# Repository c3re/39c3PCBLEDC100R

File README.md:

# 39c3PCBLEDC100R

The 39c3PCBLEDC100 is a Coaster for your drinks with option for LED and microcontroller upgrade. By stacking the coasters, you can also build nice blinky towers.

## Rev.0

### Electrical connections

Important: Do not power the board by USB and an external power supply at the same time!
The Din pin of the first LED is connected to pin D4 (GPIO2) of the Wemos D1 mini. ...well, not directly: there is a MOS-FET Transistor in between to shift the signal level from 3.3V to 5V. 
Two of the mounting holes are connected to GND, two of the holes are connected to 5V. You can use this feature to stack multiple 39c3PCBLEDc100R Boards with brass spacers.

The button is connected to D3 (GPIO0) and GND. In WLED (Time & Macros -> Button actions) you can configure actions for short, long and double click.

## License
    
39c3PCBLEDC100R © 2025 by c3RE is licensed under CC BY 4.0. To view a copy of this license,   
visit http://creativecommons.org/licenses/by/4.0/

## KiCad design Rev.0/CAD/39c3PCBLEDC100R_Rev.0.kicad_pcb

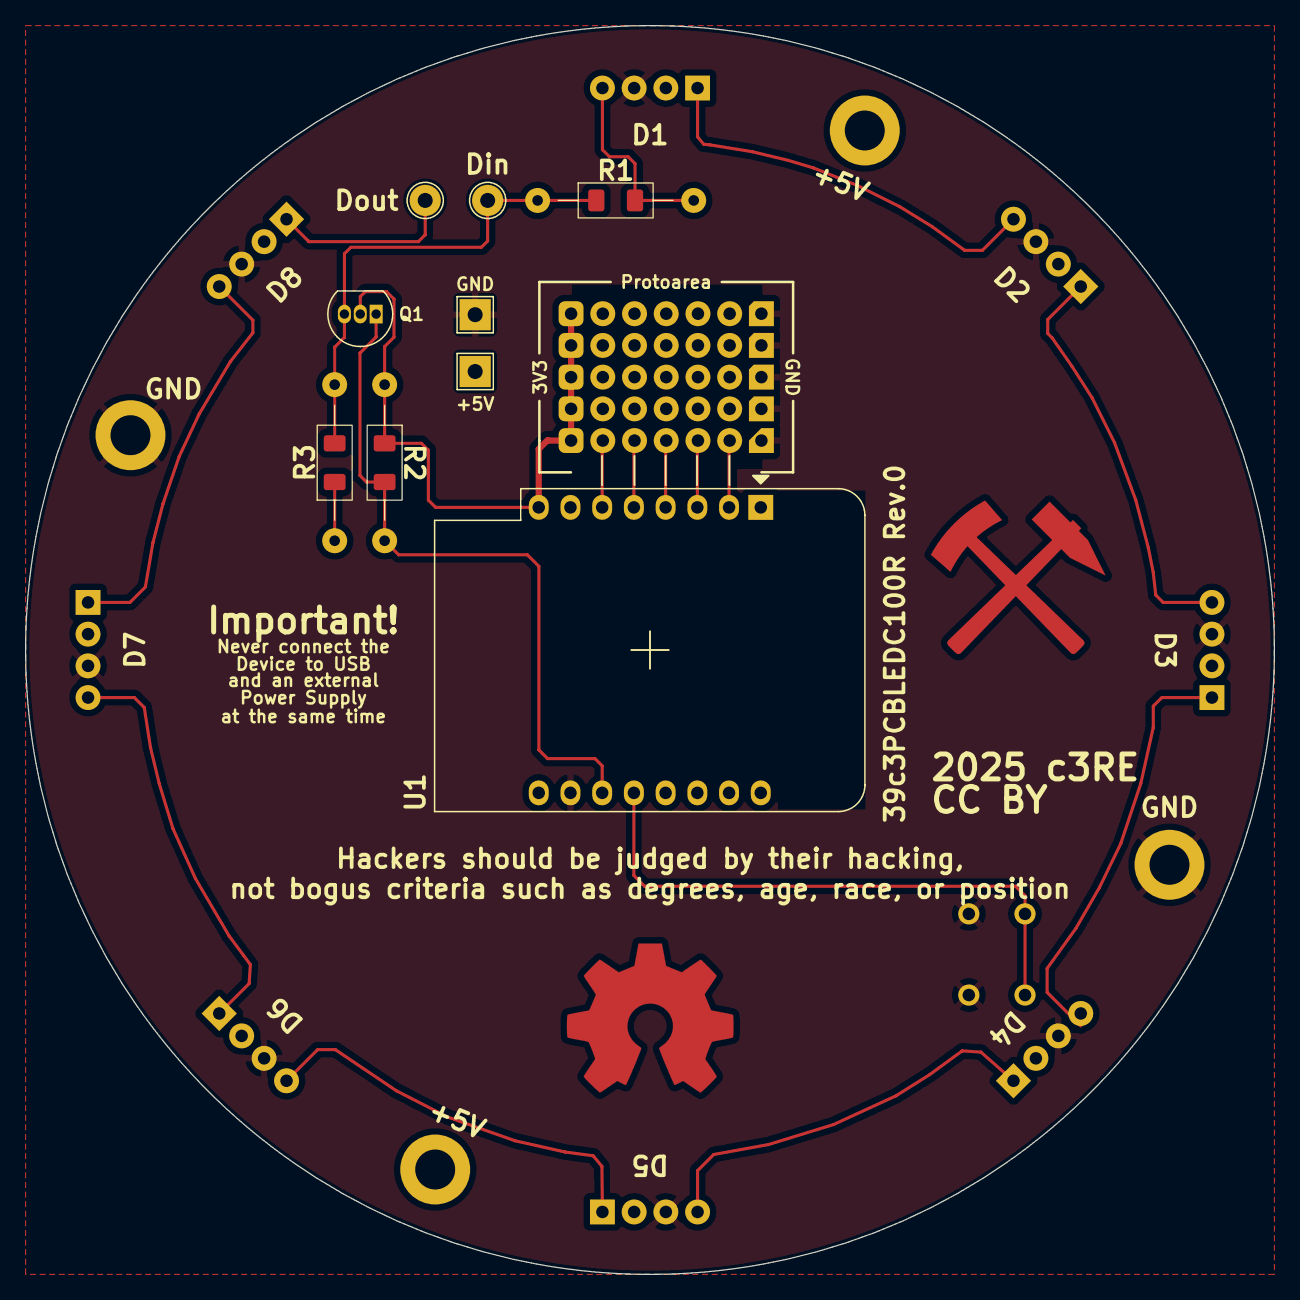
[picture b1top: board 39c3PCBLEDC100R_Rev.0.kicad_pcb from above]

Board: 2 copper layers, 100.0 x 100.0 mm, 23 parts (1 on the bottom side), 20 nets.

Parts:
+5V, +5V#2: +5V; MountingHole_3.2mm_M3_DIN965_Pad
+5V#3: +5V; TestPoint_THTPad_2.5x2.5mm_Drill1.2mm
A1: Protoarea
D1, D2, D3, D4, D5, D6, D7, D8: WS2812D-F5; WS2812_THT
Din: Din; TestPoint_THTPad_D2.5mm_Drill1.2mm
Dout: Dout; TestPoint_THTPad_D2.5mm_Drill1.2mm
GND: GND; MountingHole_3.2mm_M3_DIN965_Pad
GND#2: GND; TestPoint_THTPad_2.5x2.5mm_Drill1.2mm
GND#3: GND; MountingHole_3.2mm_M3_DIN965_Pad
Q1: ZVNL110A; TO-92_Inline
R1: 100; 1206_combi_handsolder
R2, R3: 10k; 1206_combi_handsolder
SW1: SW_SPST; SW_TH_Tactile_Omron_B3F-102x
U1: WeMos_D1_mini; WEMOS_D1_mini_light

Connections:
+5V: +5V.1, +5V#2.1, +5V#3.1, D1.2 (VCC), D2.2 (VCC), D3.2 (VCC), D4.2 (VCC), D5.2 (VCC), D6.2 (VCC), D7.2 (VCC), D8.2 (VCC), R3.1, U1.9 (5V)
/Din: Din.1, Q1.3 (D), R1.1, R3.2
/Dout: D8.1 (DOUT), Dout.1
GND: A1.7 (GND), D1.3 (GND), D2.3 (GND), D3.3 (GND), D4.3 (GND), D5.3 (GND), D6.3 (GND), D7.3 (GND), D8.3 (GND), GND.1, GND#2.1, GND#3.1, SW1.2 (B), U1.10 (GND)
unnamed: A1.8 (Vin), Q1.2 (G), R2.1, U1.8 (3V3)
unnamed: D1.4 (DIN), R1.2
unnamed: D1.1 (DOUT), D2.4 (DIN)
unnamed: D2.1 (DOUT), D3.4 (DIN)
unnamed: D3.1 (DOUT), D4.4 (DIN)
unnamed: D4.1 (DOUT), D5.4 (DIN)
unnamed: D5.1 (DOUT), D6.4 (DIN)
unnamed: D6.1 (DOUT), D7.4 (DIN)
unnamed: D7.1 (DOUT), D8.4 (DIN)
unnamed: Q1.1 (S), R2.2, U1.11 (D4)
unnamed: SW1.1 (A), U1.12 (D3)
unnamed: A1.6, U1.2 (A0)
unnamed: A1.5, U1.3 (D0)
unnamed: A1.3, U1.5 (MISO/D6)
unnamed: A1.2, U1.6 (MOSI/D7)
unnamed: A1.4, U1.4 (SCK/D5)

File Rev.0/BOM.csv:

Pos.,Qty.,Designator,Description,Manufacturer,Part-No. (Manufacturer),Vendor,Part-No. (Vendor)
1,1,R1,Metal Film Resistor 100Ohm 250mW,VICO,MF1/4W-100Ω±1%-OT52,LCSC,C2903231
2,2,R2-R3,Metal Film Resistors 10kΩ 250mW,YAGEO,MFR-25FTE52-10K,LCSC,C172967
3,1,Q1,MOSFET N-CH 100V 320MA TO92-3,Diodes Inc.,ZVNL110A,DigiKey,ZVNL110A-ND
4,8,D1-D8,D=5mm RGB LED(Built-in IC),Worldsemi,WS2812D-F5,LCSC,C190565
5,4,na,Spacer,Shuntian,M3X25+6,LCSC,C775782
6,1,SW1,Switch SPST-NO,Omron,B3F-1005,LCSC,C397293

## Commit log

2025-10-22 Added some files
2025-10-22 edited readme.md
2025-10-22 First commit of the updated Design files
2025-12-22 Update README.md
    info about Button
2025-12-23 uploaded schematic PNG and build instructions PDF
2025-12-26 add manual
2025-12-26 update new manual version
2026-01-11 Added files for production & fixed some minor errors on the silkscreen
